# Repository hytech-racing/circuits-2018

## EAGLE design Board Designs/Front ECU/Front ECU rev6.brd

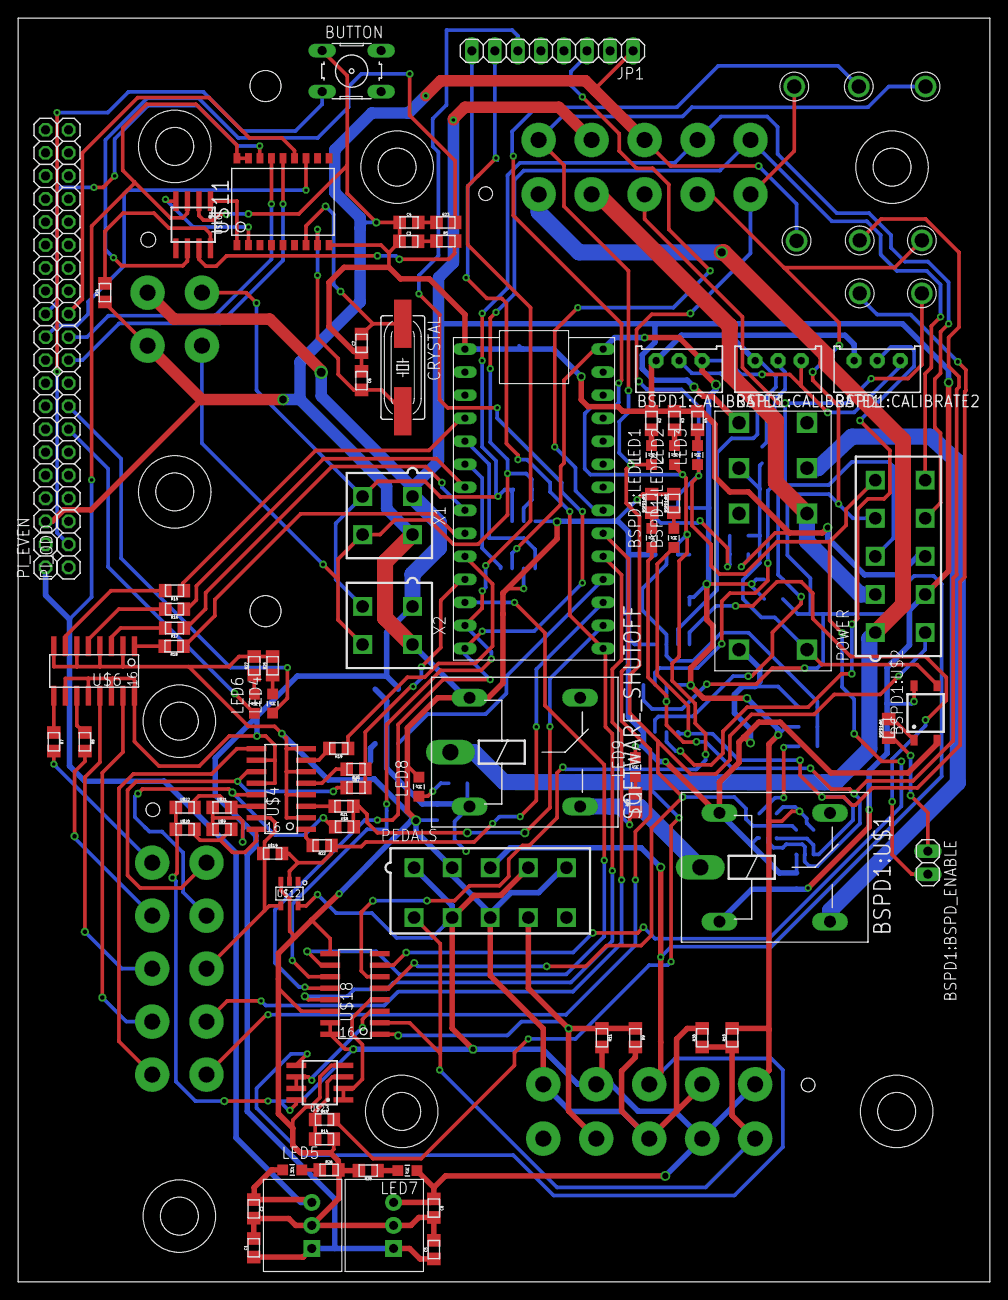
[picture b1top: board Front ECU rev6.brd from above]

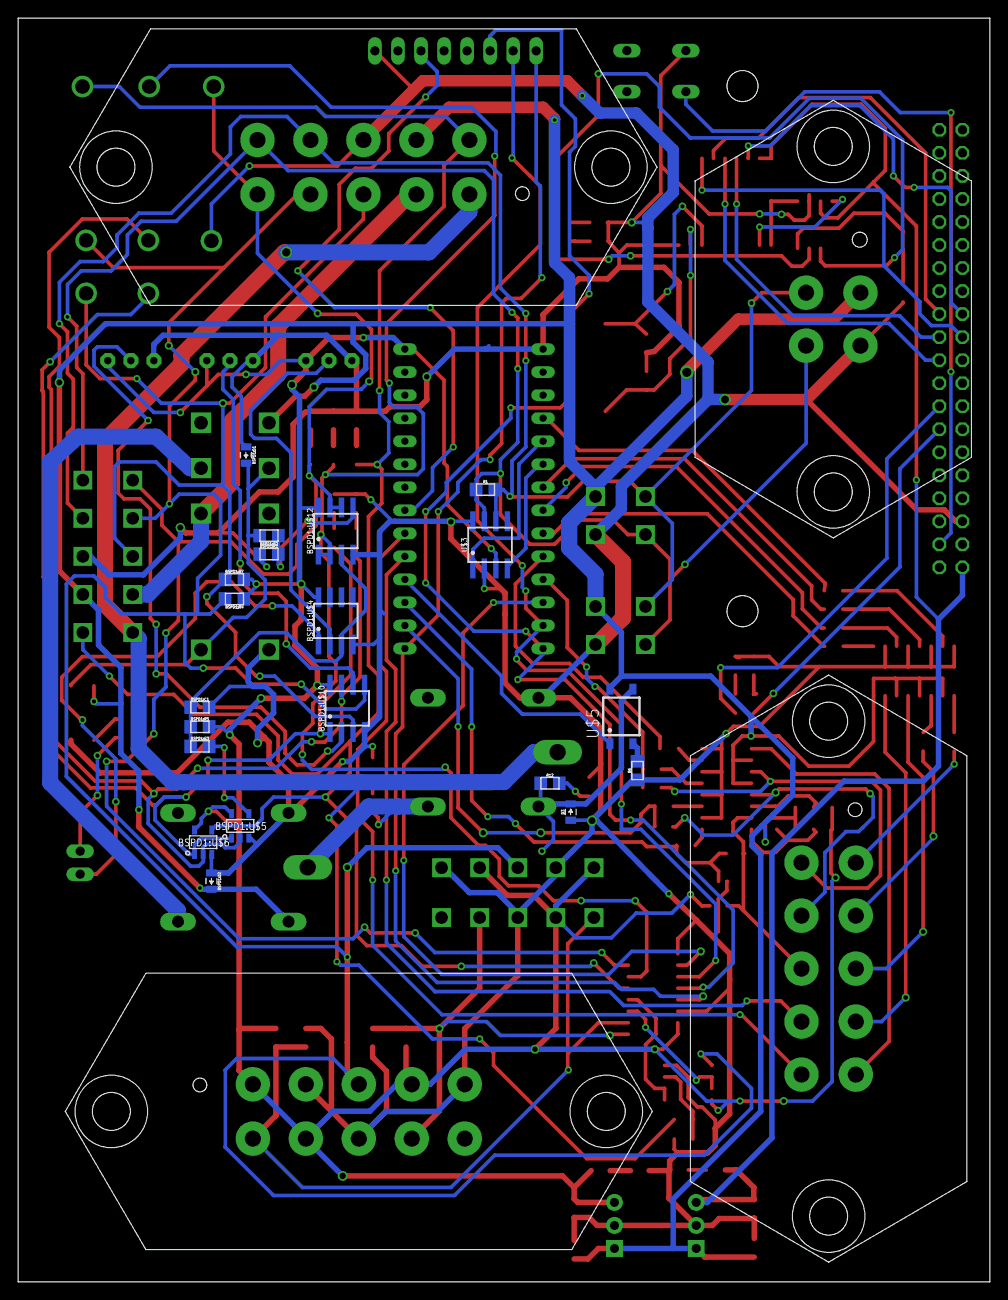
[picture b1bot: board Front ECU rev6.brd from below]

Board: 2 copper layers, 107.2 x 139.4 mm, 115 parts (24 on the bottom side), 100 nets.

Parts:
BSPD1:BSPD_ENABLE: JUMPER; 1X02
BSPD1:C1: .47u; 0805
BSPD1:CALIBRATE1, BSPD1:CALIBRATE2, BSPD1:CALIBRATE3: TRIMPOT_3296
BSPD1:D1, BSPD1:D2: DIODE0805; 0805_D
BSPD1:LED1: RED; LED-805
BSPD1:LED2: YELLOW; LED-805
BSPD1:R1: 12k; 0805
BSPD1:R2: 43k; 0805
BSPD1:R3: 330; 0805
BSPD1:R4, BSPD1:R7: 10k; 0805
BSPD1:R5: 680k; 0805
BSPD1:R6: 680; 0805
BSPD1:R8, BSPD1:R9: 270; 0805
BSPD1:U$1: G5LE; ZF112
BSPD1:U$2: CPC1002N; SOP04
BSPD1:U$3: JW2SN-DC12V; JW2SN
BSPD1:U$4, BSPD1:U$10: MCP6542SOIC; SOIC-08
BSPD1:U$5: SN74AHC1G09; SOT-23-5
BSPD1:U$6: SN74LVC1G08; SOT-23-5
BSPD1:U$11, BSPD1:U$13: TEST_POINT
BSPD1:U$12: MCP6002SOIC; SOIC-08
BUTTON: B3F-10XX
C1, C2, C5, C8: 10uF; 0805
C3, C4: 560pF; 0805
C6, C7: 22pF; 0805
CRYSTAL: 16MHz; HC49UP
D3: DIODE0805; 0805_D
IC2, IC3: OKI-78SR
JP1: 1X08
LED1, LED6, LED8, LED9: RED; LED-805
LED2: YELLOW; LED-805
LED3, LED4: GREEN; LED-805
LED5, LED7: PURPLE; LED-805
PEDALS: MINIFIT_5566-10
PI_EVEN: 1X20
PI_ODD: 1X20
POWER: MINIFIT_5566-10
R1: 120; 0805
R2, R3, R15, R16, R17, R18, R19, R20, R21, R22, R27: 270; 0805
R4, R25, R26, R28: 200; 0805
R5, R23: 100; 0805
R6: 330; 0805
R7, R8: 0; 0805
R9, R10, R11, R30: 10k; 0805
R12, R29: 1.2K; 0805
R13: 43k; 0805
R14: 12k; 0805
R24: 4.7k; 0805
SOFTWARE_SHUTOFF: G5LE; ZF112
U$1: TEENSY_3.2_SIMPLE
U$2, U$13, U$14, U$15, U$16, U$17: TEST_POINT
U$3, U$10: MCP2551; SOIC-08
U$4, U$6: TLP291-4; SOIC-16
U$5: CPC1002N; SOP04
U$7, U$8, U$9, U$19, U$20, U$21, U$22: JUMPER; 0805
U$11: MCP2515SMD; SOIC-18W
U$12: SN74LV1T34; SOT-23-5
U$18: MCP3208SOIC; SOIC-16
U$23: MCP6002SOIC; SOIC-08
X1, X2: CONNECTOR-4; MINIFIT_5566-4
X3: CONNECTOR-4MX150L_VERTICAL-4; MX150L_VERTICAL-4
X4, X5, X6: CONNECTOR-10MX150L_VERTICAL-10; MX150L_VERTICAL-10

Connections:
+5V: BSPD1:CALIBRATE1.1, BSPD1:CALIBRATE2.1, BSPD1:CALIBRATE3.1, BSPD1:R4.1, BSPD1:R5.2, BSPD1:R7.2, BSPD1:U$4.8, BSPD1:U$5.5, BSPD1:U$6.5, BSPD1:U$10.8, BSPD1:U$12.8, C8.1, IC3.3, LED7.A, PEDALS.1, PEDALS.4, PEDALS.7, R10.2, R11.2, U$1.VIN, U$3.3, U$12.5, U$18.15, U$18.16, U$20.1, U$22.1, U$23.8, X4.1, X4.4, X4.7
+5V/1: C2.1, IC2.3, LED5.A, PI_EVEN.1, U$10.3, U$11.17, U$11.18
+12V: BSPD1:D2.C, BSPD1:U$1.2, BSPD1:U$2.4, BSPD1:U$3.4, C1.1, C5.1, IC2.1, IC3.1, POWER.7, U$4.10, U$4.12, U$5.4, U$6.10, U$6.12, U$6.14, U$6.16, U$9.1, U$21.1, X1.1, X2.1, X3.1, X5.7
BSPD1:N$1: BSPD1:D1.C, BSPD1:R2.2, BSPD1:U$2.3, BSPD1:U$3.3, BSPD1:U$3.COIL-
BSPD1:N$2: BSPD1:R3.2, BSPD1:U$5.4
BSPD1:N$3: BSPD1:R6.2, BSPD1:U$2.1
BSPD1:N$4: BSPD1:BSPD_ENABLE.1, BSPD1:R6.1
BSPD1:N$5: BSPD1:CALIBRATE2.2, BSPD1:U$10.2
BSPD1:N$6: BSPD1:CALIBRATE1.2, BSPD1:U$10.6
BSPD1:N$7: BSPD1:CALIBRATE3.2, BSPD1:U$4.2
BSPD1:N$8: BSPD1:BSPD_ENABLE.2, BSPD1:U$4.1
BSPD1:N$9: BSPD1:R1.2, BSPD1:R2.1, BSPD1:U$12.5
BSPD1:N$13: BSPD1:C1.1, BSPD1:R3.1, BSPD1:R5.1, BSPD1:U$4.3, BSPD1:U$12.3
BSPD1:N$14: BSPD1:LED2.C, BSPD1:R8.1
BSPD1:N$15: BSPD1:LED1.C, BSPD1:R9.1
BSPD1:N$16: BSPD1:LED1.A, BSPD1:U$5.2, BSPD1:U$6.2, BSPD1:U$10.7, BSPD1:U$11.P$1
BSPD1:N$17: BSPD1:LED2.A, BSPD1:U$5.1, BSPD1:U$6.1, BSPD1:U$10.1, BSPD1:U$13.P$1
BSPD1:SHUTDOWN_C: BSPD1:U$1.S, BSPD1:U$3.6
BUT: BUTTON.3, PI_ODD.2
CAN-H: R5.2, U$10.7
CAN-L: R23.2, U$10.6
CANH: POWER.10, R1.1, U$3.7, X1.4, X2.4, X3.4, X5.10
CANL: POWER.9, R1.2, U$3.6, X1.3, X2.3, X3.3, X5.9
CS: PI_EVEN.12, U$11.16
CS_ADXL345: JP1.3, U$1.A5
CS_MCP3208: U$1.D10(TX2), U$18.10
DASH_CTRL1: R15.1, U$1.D2
DASH_CTRL2: R16.1, U$1.D5
DASH_CTRL3: R17.1, U$1.D6
DASH_CTRL4: R18.1, U$1.D7(RX3)
DASH_CTRL5: R19.1, U$1.D8(TX3)
DASH_CTRL6: R20.1, U$1.D9(RX2), U$7.2
DASH_CTRL7: R21.1, U$1.A0, U$8.2
DASH_CTRL8: R22.1, U$1.A1, U$12.2, U$19.2
DASH_CTRL9: U$1.A3, X6.9
DASH_CTRL10: U$1.A4, X6.10
DASH_IO1: R7.2, X6.1
DASH_IO2: R8.2, X6.2
DASH_IO3: U$6.13, X6.3
DASH_IO4: U$6.15, X6.4
DASH_IO5: U$4.9, X6.5
DASH_IO6: U$4.11, U$7.1, X6.6
DASH_IO7: U$4.13, U$8.1, X6.7
DASH_IO8: U$4.15, U$12.4, U$19.1, X6.8
GND: BSPD1:C1.2, BSPD1:CALIBRATE1.3, BSPD1:CALIBRATE2.3, BSPD1:CALIBRATE3.3, BSPD1:D1.A, BSPD1:D2.A, BSPD1:R1.1, BSPD1:R8.2, BSPD1:R9.2, BSPD1:U$1.1, BSPD1:U$2.2, BSPD1:U$3.COIL+, BSPD1:U$4.4, BSPD1:U$5.3, BSPD1:U$6.3, BSPD1:U$10.4, BSPD1:U$12.4, BUTTON.1, C1.2, C2.2, C3.1, C4.1, C5.2, C6.1, C7.1, C8.2, D3.A, IC2.2, IC3.2, JP1.1, LED8.C, LED9.C, PEDALS.2, PEDALS.5, PEDALS.8, PI_EVEN.3, POWER.8, R2.1, R3.1, R4.1, R6.1, R9.2, R14.2, R24.1, R25.2, R26.2, R27.2, R28.2, R30.2, SOFTWARE_SHUTOFF.1, U$1.GND, U$2.P$1, U$3.2, U$3.8, U$4.2, U$4.4, U$4.6, U$4.8, U$6.2, U$6.4, U$6.6, U$6.8, U$10.2, U$11.9, U$12.3, U$18.9, U$18.14, U$23.4, X1.2, X2.2, X3.2, X4.2, X4.5, X4.8, X5.8
INT: PI_EVEN.11, U$11.12
LED1: LED4.A, PI_ODD.8
LED2: LED6.A, PI_ODD.7
MISO: PI_ODD.11, U$11.15
MISO_TEENSY: JP1.6, U$1.D12, U$18.12
MOSI: PI_ODD.10, U$11.14
MOSI_TEENSY: JP1.7, U$1.D11, U$18.11
unnamed: R7.1, U$6.9
unnamed: U$1.D4(CANRX), U$3.4
unnamed: R8.1, U$6.11
unnamed: U$4.16, U$9.2, U$20.2
unnamed: U$1.D3(CANTX), U$3.1
unnamed: U$4.14, U$21.2, U$22.2
unnamed: R13.1, R14.1, U$23.3
unnamed: LED8.A, R12.2
unnamed: LED9.A, R29.2
unnamed: D3.C, R12.1, SOFTWARE_SHUTOFF.2, U$5.3
unnamed: LED1.C, R2.2
unnamed: LED2.C, R3.2
unnamed: LED3.C, R4.2
unnamed: R15.2, U$6.7
unnamed: R6.2, U$5.2
unnamed: R16.2, U$6.5
unnamed: R21.2, U$4.3
unnamed: R17.2, U$6.3
unnamed: R18.2, U$6.1
unnamed: R19.2, U$4.7
unnamed: R20.2, U$4.5
unnamed: R22.2, U$4.1
unnamed: U$10.1, U$11.1
unnamed: U$10.4, U$11.2
unnamed: C6.2, CRYSTAL.2, U$11.8
unnamed: R24.2, U$10.8
unnamed: C7.2, CRYSTAL.1, U$11.7
unnamed: C3.2, R5.1
unnamed: C4.2, R23.1
unnamed: LED4.C, R25.1
unnamed: LED5.C, R26.1
unnamed: LED6.C, R27.1
unnamed: LED7.C, R28.1
READ_BRAKE: U$18.3, U$23.6, U$23.7
READ_CHARGE: BSPD1:U$12.1, BSPD1:U$12.2, LED2.A, U$16.P$1, U$18.6
READ_FAULT: BSPD1:U$12.6, BSPD1:U$12.7, LED3.A, POWER.5, U$15.P$1, U$18.7, X5.5
READ_SWITCH: BSPD1:U$6.4, LED1.A, POWER.6, U$17.P$1, U$18.5, X5.6
READ_UPSTREAM_SHUTDOWN: U$18.4, U$23.1, U$23.2
SCK: PI_ODD.12, U$11.13
SCK_TEENSY: JP1.8, U$1.D13, U$18.13
SHUTDOWN_A: POWER.1, R13.2, SOFTWARE_SHUTOFF.P, X5.1
SHUTDOWN_B: BSPD1:U$1.P, R29.1, SOFTWARE_SHUTOFF.S
SHUTDOWN_D: BSPD1:U$3.7, POWER.2, X5.2
SHUTDOWN_RELAY_CTRL: U$1.A2, U$5.1
SIGNAL_ACCEL1: PEDALS.9, R9.1, R11.1, U$18.1, X4.9
SIGNAL_ACCEL2: PEDALS.6, R10.1, R30.1, U$18.2, X4.6
SIGNAL_BRAKE: BSPD1:R4.2, BSPD1:U$10.5, PEDALS.3, POWER.4, U$13.P$1, U$23.5, X4.3, X5.4
SIGNAL_CURRENT: BSPD1:R7.1, BSPD1:U$10.3, POWER.3, U$14.P$1, X5.3

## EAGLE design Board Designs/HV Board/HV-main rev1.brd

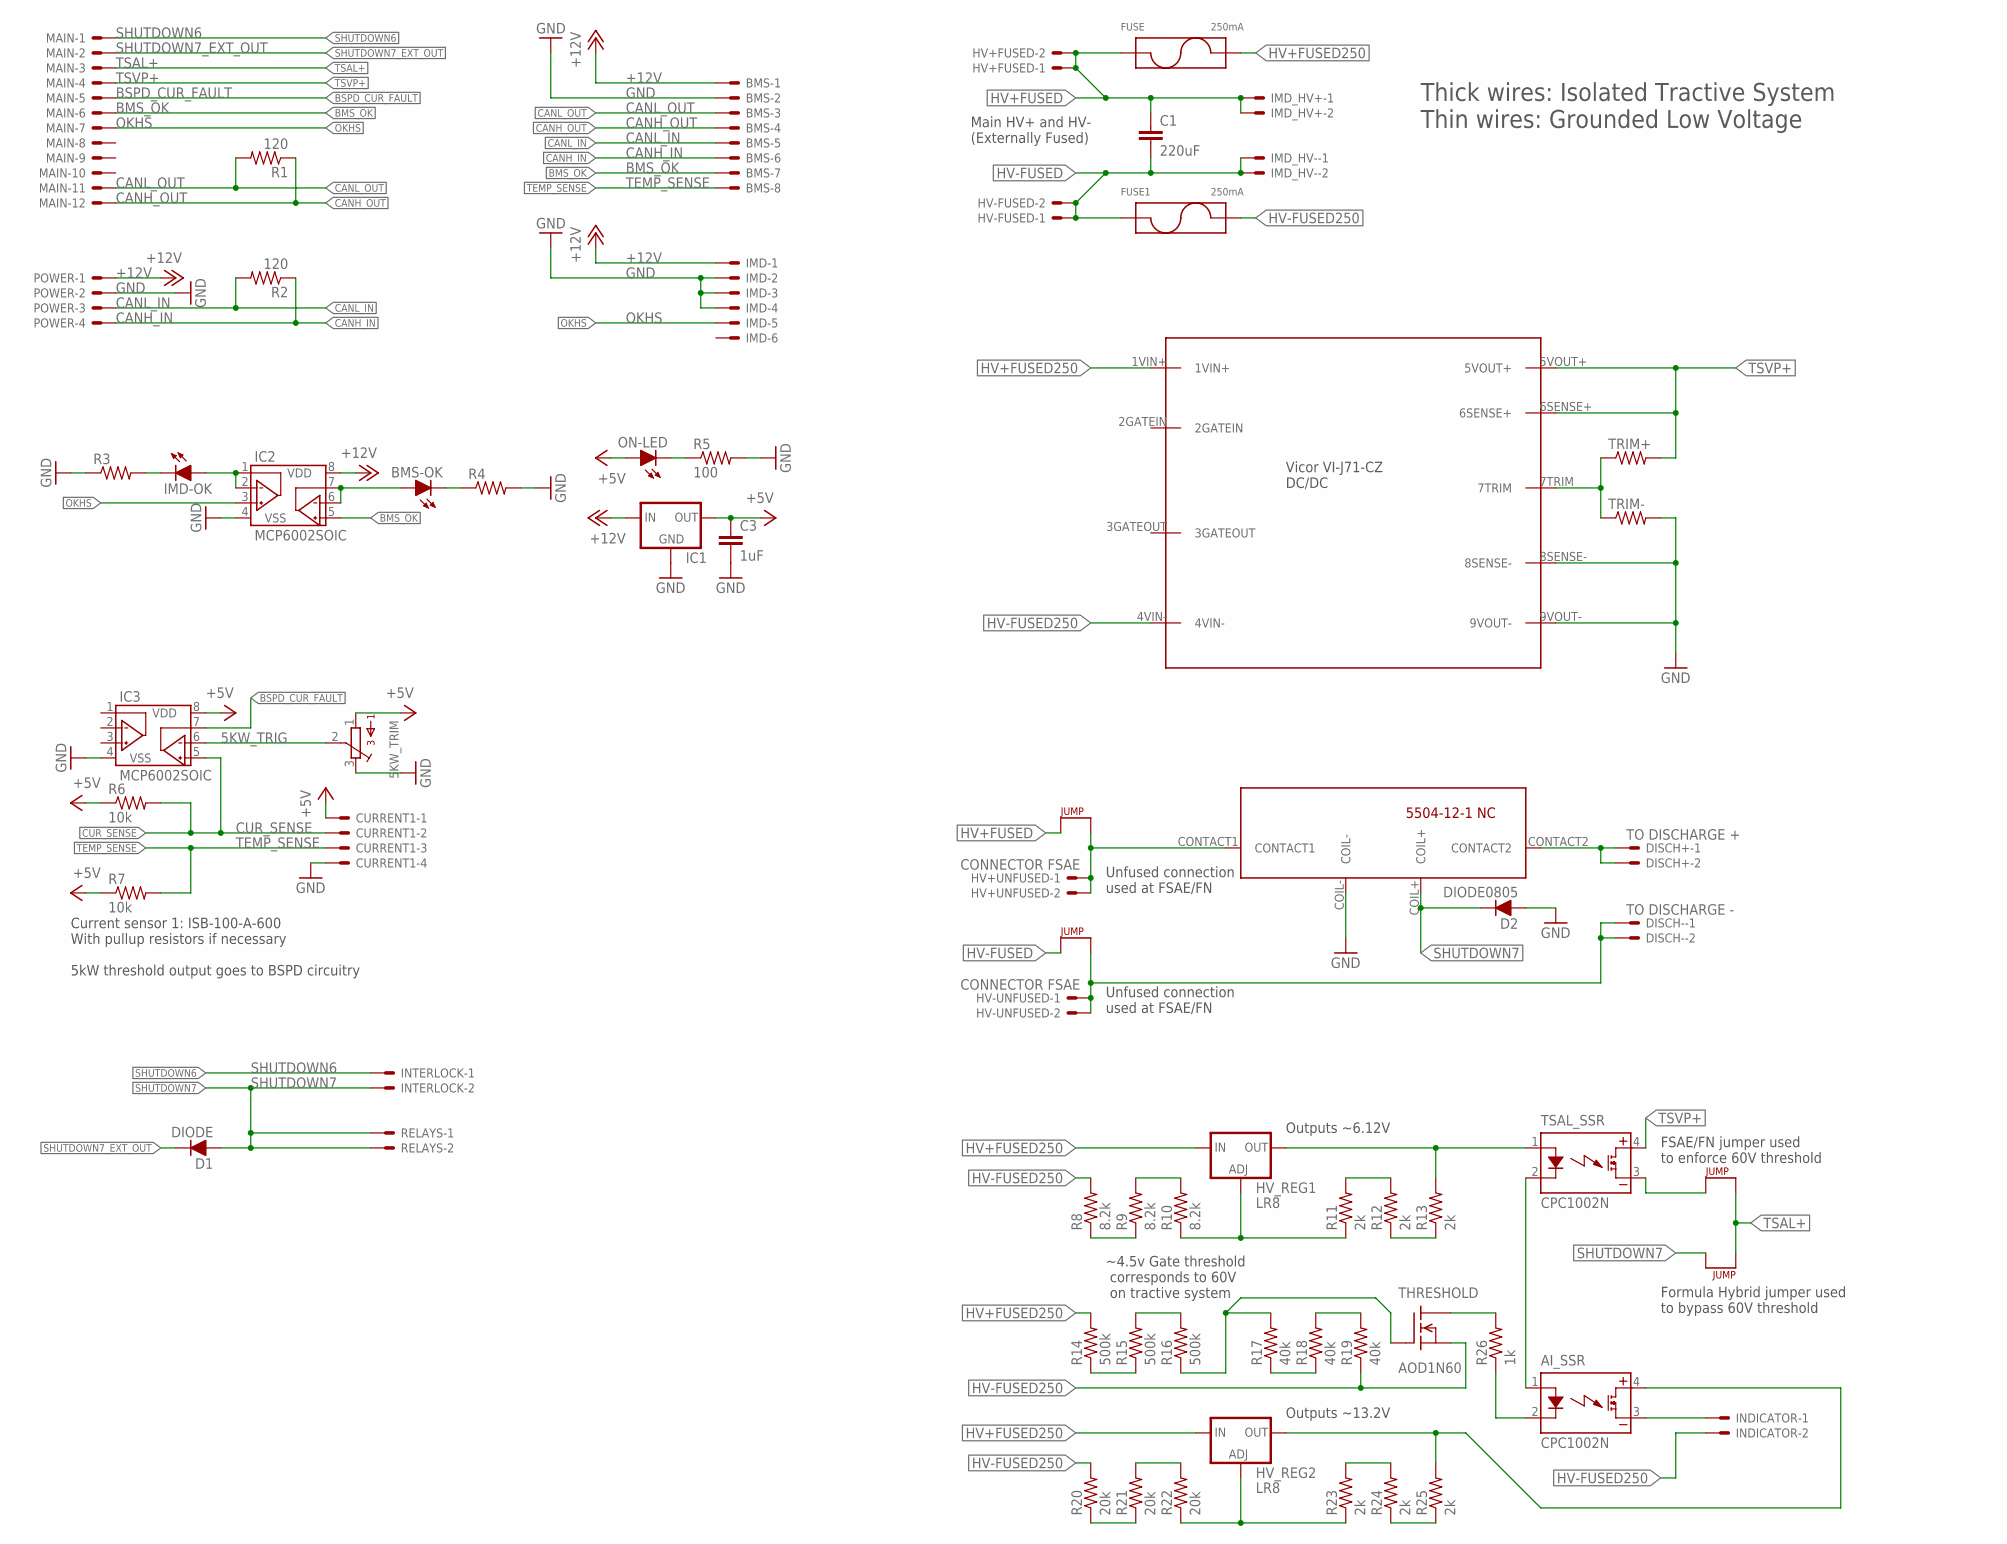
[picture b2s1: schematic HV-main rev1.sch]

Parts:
5KW_TRIM: TRIMPOT_3296C; TRIMPOT_3296
AI_SSR: CPC1002N; SOP04
BMS: MINIFIT_5566-8
BMS-OK: LED-0805; LED-805
C1: 220uF; LLS2V221MELZ
C3: 1uF; 0805
CURRENT1: MINIFIT_5566-4
D1: DIODE; DO-41
D2: DIODE0805; 0805_D
DISCH+: TO DISCHARGE +; MINIFIT_5566-2
DISCH-: TO DISCHARGE -; MINIFIT_5566-2
FUSE, FUSE1: 250mA; 1A3400_38.1MM
HV+FUSED: MINIFIT_5566-2
HV+UNFUSED: CONNECTOR FSAE; MINIFIT_5566-2
HV-FUSED: MINIFIT_5566-2
HV-UNFUSED: CONNECTOR FSAE; MINIFIT_5566-2
HV_REG1, HV_REG2: LR8; TO-252
IC1: 5VREG_L7805_VERT; TO-220
IC2, IC3: MCP6002SOIC; SOIC-08
IMD: CONNECTOR-6; MINIFIT_5566-6
IMD-OK: LED-0805; LED-805
IMD_HV+: CONNECTOR-2; MINIFIT_5566-2
IMD_HV-: CONNECTOR-2; MINIFIT_5566-2
INDICATOR: MINIFIT_5566-2
INTERLOCK: MINIFIT_5566-2
MAIN: CONNECTOR-12; MINIFIT_5566-12
ON-LED: LED-0805; LED-805
POWER: MINIFIT_5566-4
R1, R2: 120; 0805
R3, R4: RESISTOR0805-RES; 0805
R5: 100; 0805
R6, R7: 10k; 0805
R8, R9, R10: 8.2k; 0805
R11, R12, R13, R23, R24, R25: 2k; 0805
R14, R15, R16: 500k; 0805
R17, R18, R19: 40k; 0805
R20, R21, R22: 20k; 0805
R26: 1k; 0805
RELAYS: MINIFIT_5566-2
THRESHOLD: AOD1N60; TO-252
TRIM+: RESISTOR0805-RES; 0805
TRIM-: RESISTOR0805-RES; 0805
TSAL_SSR: CPC1002N; SOP04
U$1, U$2, U$3, U$4: JUMPER.3; AXIAL-0.3
U$5: HV_DCDC_VI-J71-CZ
U$12: 5504-12-1-NC

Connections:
5KW_TRIG: 5KW_TRIM.2, IC3.6 (VINB-)
+5V: 5KW_TRIM.1, C3.1, CURRENT1.1, IC1.3 (OUT), IC3.8 (VDD), ON-LED.A, R6.1, R7.1
+12V: BMS.1, IC1.1 (IN), IC2.8 (VDD), IMD.1, POWER.1
BMS_OK: BMS.7, IC2.5 (VINB+), MAIN.6
BSPD_CUR_FAULT: IC3.7 (VOUTB), MAIN.5
CANH_IN: BMS.6, POWER.4, R2.1
CANH_OUT: BMS.4, MAIN.12, R1.1
CANL_IN: BMS.5, POWER.3, R2.2
CANL_OUT: BMS.3, MAIN.11, R1.2
CUR_SENSE: CURRENT1.2, IC3.5 (VINB+), R6.2
DISCHARGE1: HV+UNFUSED.1, HV+UNFUSED.2, U$3.P$2, U$12.CONTACT1
DISCHARGE2: DISCH+.1, DISCH+.2, U$12.CONTACT2
DISCHARGE3: DISCH-.1, DISCH-.2, HV-UNFUSED.1, HV-UNFUSED.2, U$4.P$2
GND: 5KW_TRIM.3, BMS.2, C3.2, CURRENT1.4, D2.A, IC1.2 (GND), IC2.4 (VSS), IC3.4 (VSS), IMD.2, IMD.3, IMD.4, POWER.2, R3.1, R4.2, R5.2, TRIM-.2, U$5.8SENSE-, U$5.9VOUT-, U$12.COIL-
HV+FUSED: C1.P$1 (1), FUSE.P1, FUSE.P2 (P1), HV+FUSED.1, HV+FUSED.2, IMD_HV+.1, IMD_HV+.2, U$3.P$1
HV+FUSED250: FUSE.N3 (P2), FUSE.N4 (P2), HV_REG1.1 (IN), HV_REG2.1 (IN), R14.2, U$5.1VIN+
HV-FUSED: C1.P$2 (2), FUSE1.P1, FUSE1.P2 (P1), HV-FUSED.1, HV-FUSED.2, IMD_HV-.1, IMD_HV-.2, U$4.P$1
HV-FUSED250: FUSE1.N3 (P2), FUSE1.N4 (P2), INDICATOR.2, R8.2, R19.1, R20.2, THRESHOLD.3 (S), U$5.4VIN-
unnamed: AI_SSR.4 (DC+), HV_REG2.2(TAB) (OUT), R25.2
unnamed: HV_REG1.2(TAB) (OUT), R13.2, TSAL_SSR.1 (CONTROL+)
unnamed: ON-LED.C, R5.1
unnamed: TSAL_SSR.3 (DC-), U$1.P$1
unnamed: AI_SSR.2 (CONTROL-), R26.1
unnamed: AI_SSR.1 (CONTROL+), TSAL_SSR.2 (CONTROL-)
unnamed: AI_SSR.3 (DC-), INDICATOR.1
unnamed: R8.1, R9.1
unnamed: R26.2, THRESHOLD.2(TAB) (D)
unnamed: R14.1, R15.1
unnamed: R15.2, R16.2
unnamed: R17.1, R18.1
unnamed: R18.2, R19.2
unnamed: R9.2, R10.2
unnamed: HV_REG2.3 (ADJ), R22.1, R23.1
unnamed: R11.2, R12.2
unnamed: R12.1, R13.1
unnamed: HV_REG1.3 (ADJ), R10.1, R11.1
unnamed: R23.2, R24.2
unnamed: R24.1, R25.1
unnamed: R21.2, R22.2
unnamed: R16.1, R17.2, THRESHOLD.1 (G)
unnamed: R20.1, R21.1
unnamed: IC2.1 (VOUTA), IC2.2 (VINA-), IMD-OK.A
unnamed: BMS-OK.A, IC2.6 (VINB-), IC2.7 (VOUTB)
unnamed: BMS-OK.C, R4.1
unnamed: IMD-OK.C, R3.2
OKHS: IC2.3 (VINA+), IMD.5, MAIN.7
SHUTDOWN6: INTERLOCK.1, MAIN.1
SHUTDOWN7: D1.A, D2.C, INTERLOCK.2, RELAYS.1, RELAYS.2, U$2.P$2, U$12.COIL+
SHUTDOWN7_EXT_OUT: D1.C, MAIN.2
TEMP_SENSE: BMS.8, CURRENT1.3, R7.2
TRIM: TRIM+.1, TRIM-.1, U$5.7TRIM
TSAL+: MAIN.3, U$1.P$2, U$2.P$1
TSVP+: MAIN.4, TRIM+.2, TSAL_SSR.4 (DC+), U$5.5VOUT+, U$5.6SENSE+

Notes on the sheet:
Formula Hybrid jumper used to bypass 60V threshold
Current sensor 1: ISB-100-A-600 With pullup resistors if necessary 5kW threshold output goes to BSPD circuitry
Unfused connection used at FSAE/FN
FSAE/FN jumper used to enforce 60V threshold
Main HV+ and HV- (Externally Fused)
~4.5v Gate threshold corresponds to 60V on tractive system
Thick wires: Isolated Tractive System Thin wires: Grounded Low Voltage
Outputs ~6.12V
Outputs ~13.2V

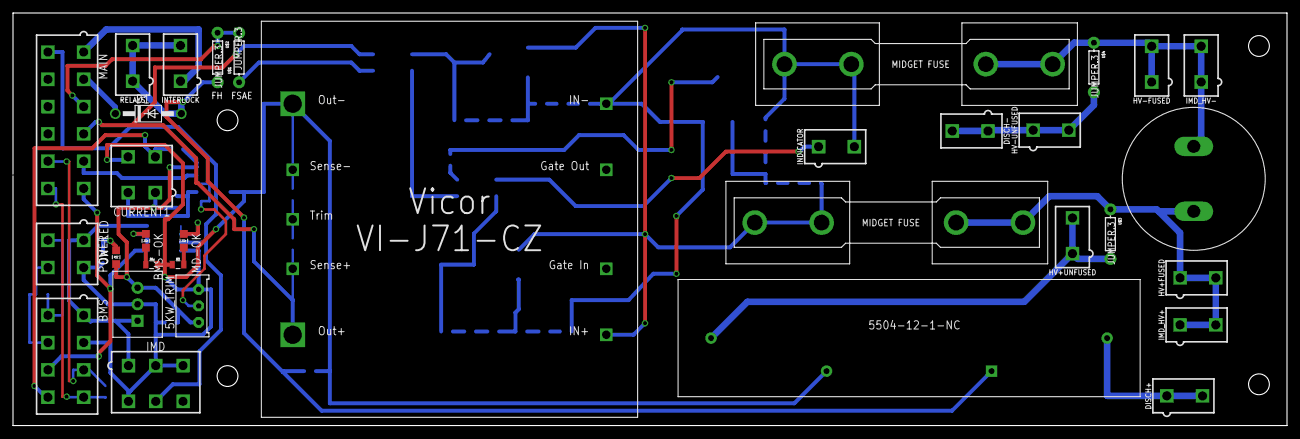
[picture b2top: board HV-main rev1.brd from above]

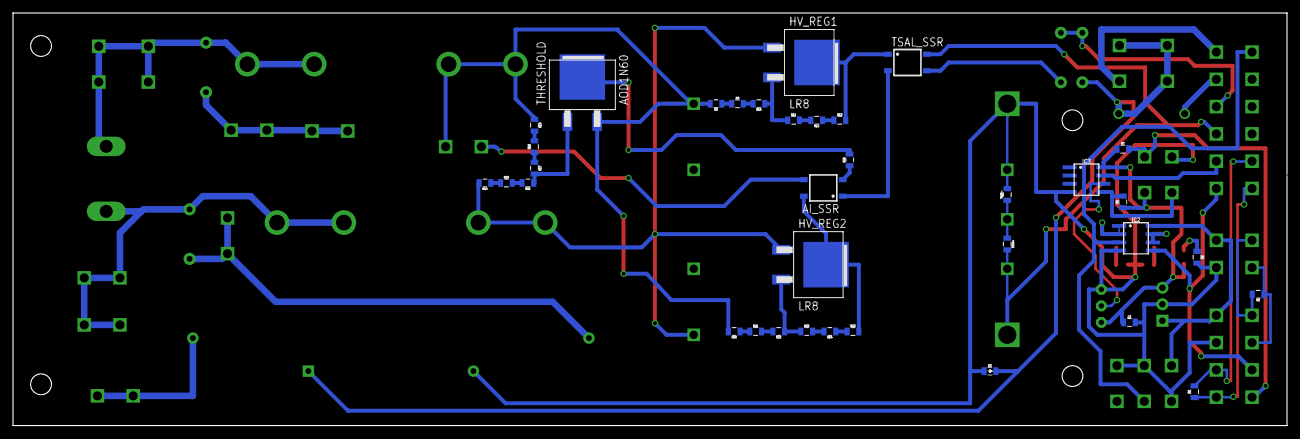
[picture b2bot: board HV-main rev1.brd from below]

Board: 2 copper layers, 196.1 x 63.5 mm, 68 parts (35 on the bottom side), 53 nets.

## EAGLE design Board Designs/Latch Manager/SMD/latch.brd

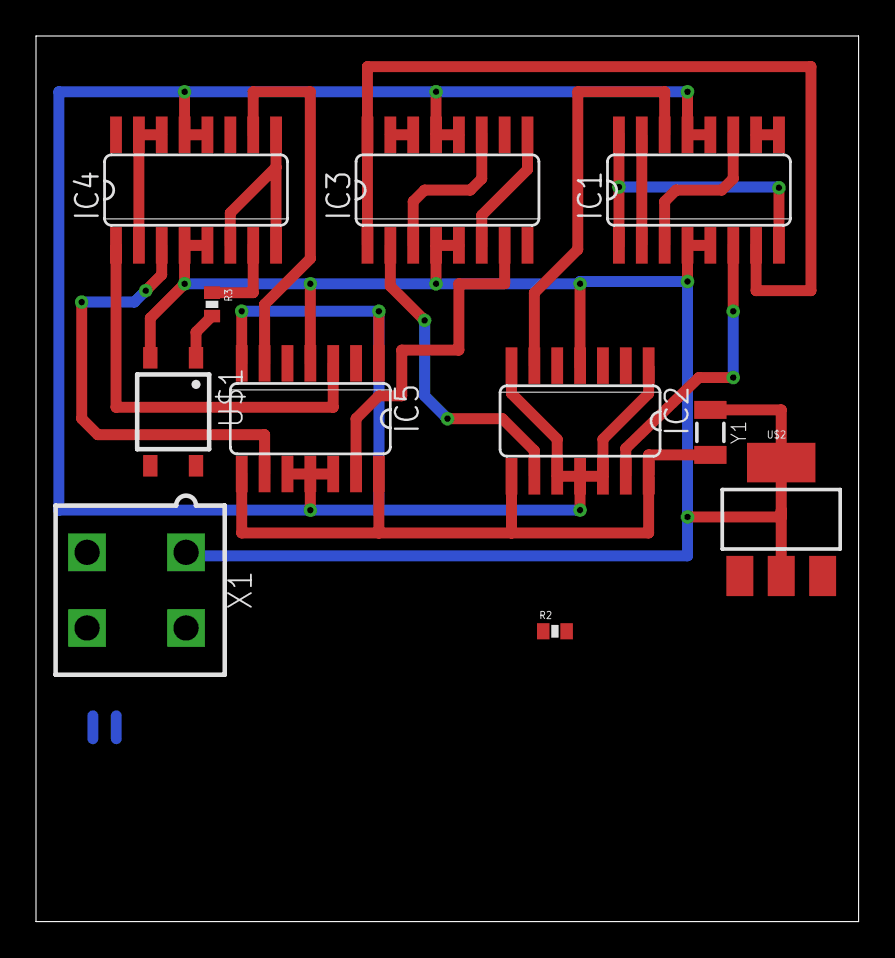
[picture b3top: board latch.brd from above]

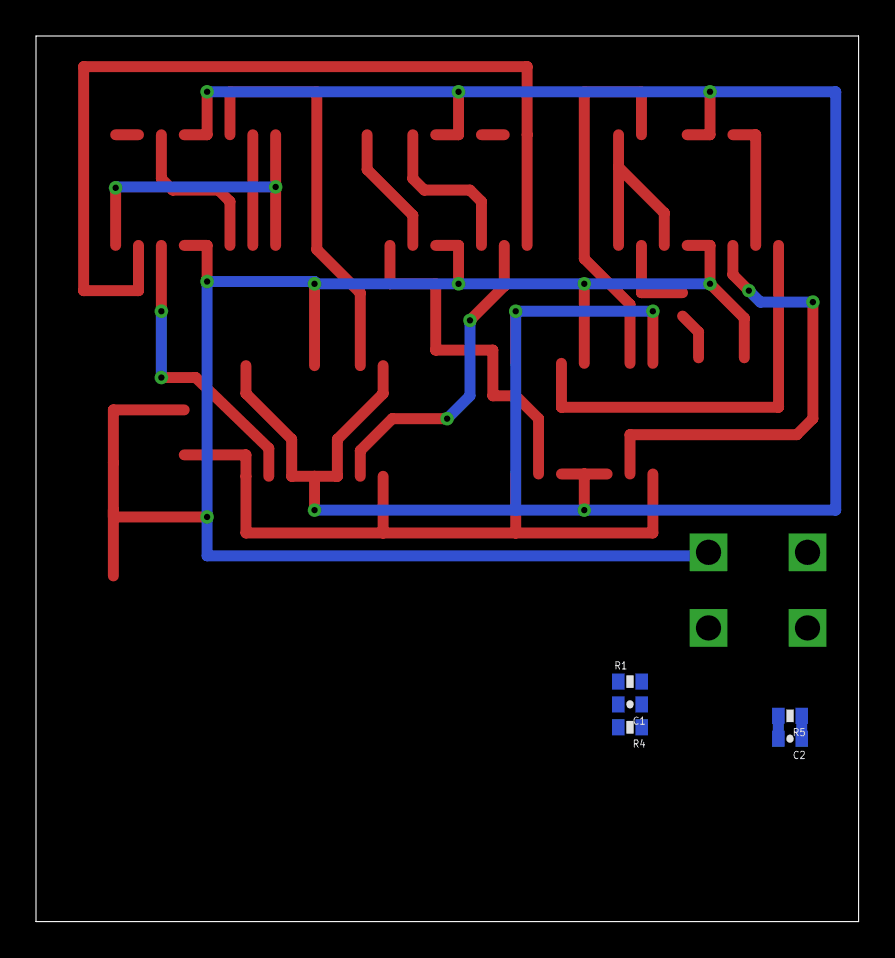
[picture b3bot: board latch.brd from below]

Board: 2 copper layers, 45.7 x 49.2 mm, 16 parts (5 on the bottom side), 25 nets.

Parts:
C1, C2: 0402-CAP
IC1, IC3, IC4: 74AC11000D; SO16
IC2, IC5: 74AC11074D; SO14
R1, R2, R3, R4, R5: 0402-RES
U$1: CPC1002N; SOP04
U$2: SOT223
X1: CONNECTOR-4; MINIFIT_5566-4
Y1: 16MHz; CRYSTAL-SMD-3.2X1.5MM

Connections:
+5V: IC1.12, IC1.13, IC2.1, IC2.7, IC2.10, IC2.11, IC2.12, IC3.12, IC3.13, IC4.12, IC4.13, IC5.1, IC5.7, IC5.10, IC5.11, IC5.12, R1.1, R2.2, U$2.3
GND: IC1.4, IC1.5, IC2.4, IC3.4, IC3.5, IC4.4, IC4.5, IC5.4, U$1.2, U$2.2, U$2.4, X1.1, Y1.P$1
unnamed: C2.1, R2.1, R5.1, X1.4
unnamed: IC1.2, IC1.15
unnamed: C2.2, IC1.1, IC1.8, IC1.16, R5.2
unnamed: IC1.3, IC1.11
unnamed: IC1.9, IC1.10, IC2.3
unnamed: IC1.6, IC2.13
unnamed: IC2.8, IC2.14, IC5.8, IC5.14, Y1.P$2
unnamed: IC2.9, IC3.2
unnamed: IC1.14, IC2.6, IC4.11
unnamed: IC4.3, IC5.9
unnamed: IC1.7, IC3.1, IC3.16
unnamed: IC4.7, R3.1
unnamed: R3.2, U$1.1
unnamed: C1.2, IC3.14, IC3.15, R4.2
unnamed: C1.1, R1.2, R4.1, X1.3
unnamed: U$2.1, X1.2
unnamed: IC3.3, IC3.11
unnamed: IC3.6, IC3.9
unnamed: IC3.8, IC4.1, IC5.3
unnamed: IC3.7, IC5.13
unnamed: IC3.10, IC4.10, IC5.6
unnamed: IC4.2, IC4.14, IC4.15
unnamed: IC4.6, IC4.8, IC4.9

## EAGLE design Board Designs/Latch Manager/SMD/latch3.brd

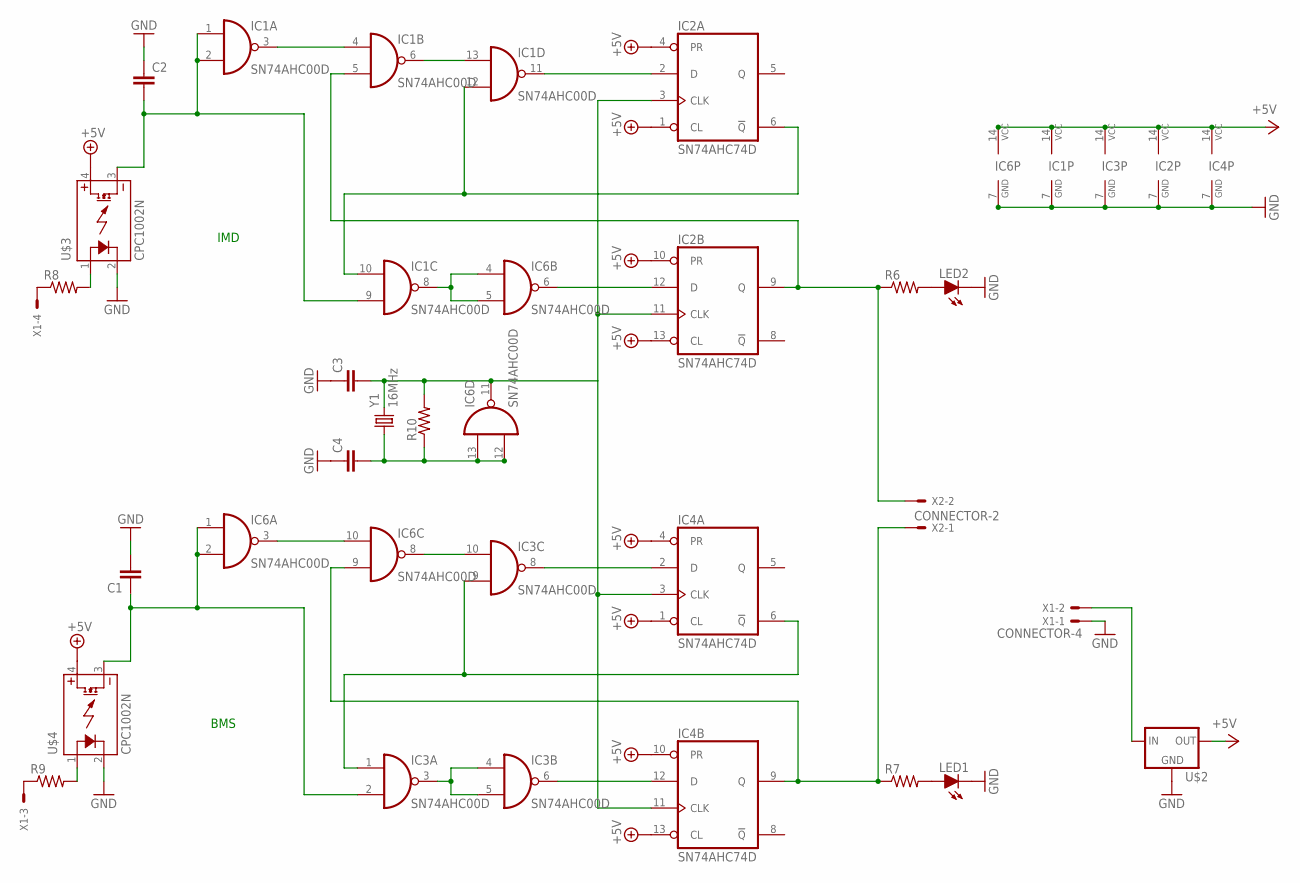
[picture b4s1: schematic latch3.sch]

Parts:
C1, C2, C3, C4: CAP0402-CAP; 0402-CAP
IC1, IC3, IC6: SN74AHC00D; SOIC-14
IC2, IC4: SN74AHC74D; SOIC-14
LED1, LED2: LED-0805; LED-805
R6, R7, R8, R9, R10: RESISTOR0402; 0402-RES
U$2: 5VREG_LM340-NLM340MPX-5.0/NOPB; SOT223
U$3, U$4: CPC1002N; SOP04
X1: CONNECTOR-4; MINIFIT_5566-4
X2: CONNECTOR-2; MINIFIT_5566-2
Y1: 16MHz; CRYSTAL-SMD-3.2X1.5MM

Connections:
12V: U$2.1 (IN), X1.2
+5V: IC1.14 (VCC), IC2.1 (CL), IC2.4 (PR), IC2.10 (PR), IC2.13 (CL), IC2.14 (VCC), IC3.14 (VCC), IC4.1 (CL), IC4.4 (PR), IC4.10 (PR), IC4.13 (CL), IC4.14 (VCC), IC6.14 (VCC), U$2.3 (OUT), U$3.4 (DC+), U$4.4 (DC+)
BMS_5V: C1.1, IC3.2 (I1), IC6.1 (I0), IC6.2 (I1), U$4.3 (DC-)
BMS_IN: R9.2, U$4.1 (CONTROL+)
BMS_OUT: IC4.9 (Q), IC6.9 (I1), R7.1, X2.1
GND: C1.2, C2.1, C3.1, C4.1, IC1.7 (GND), IC2.7 (GND), IC3.7 (GND), IC4.7 (GND), IC6.7 (GND), LED1.C, LED2.C, U$2.2 (GND), U$2.4 (GND), U$3.2 (CONTROL-), U$4.2 (CONTROL-), X1.1
IMD_5V: C2.2, IC1.1 (I0), IC1.2 (I1), IC1.9 (I1), U$3.3 (DC-)
IMD_IN: R8.2, U$3.1 (CONTROL+)
IMD_OUT: IC1.5 (I1), IC2.9 (Q), R6.1, X2.2
unnamed: IC1.3 (O), IC1.4 (I0)
unnamed: IC1.6 (O), IC1.13 (I0)
unnamed: IC1.10 (I0), IC1.12 (I1), IC2.6 (!Q)
unnamed: IC1.11 (O), IC2.2 (D)
unnamed: C3.2, IC2.3 (CLK), IC2.11 (CLK), IC4.3 (CLK), IC4.11 (CLK), IC6.11 (O), R10.2, Y1.P$2 (2)
unnamed: IC2.12 (D), IC6.6 (O)
unnamed: IC3.6 (O), IC4.12 (D)
unnamed: IC1.8 (O), IC6.4 (I0), IC6.5 (I1)
unnamed: C4.2, IC6.12 (I1), IC6.13 (I0), R10.1, Y1.P$1 (1)
unnamed: IC6.3 (O), IC6.10 (I0)
unnamed: IC3.10 (I0), IC6.8 (O)
unnamed: IC3.1 (I0), IC3.9 (I1), IC4.6 (!Q)
unnamed: IC3.8 (O), IC4.2 (D)
unnamed: IC3.3 (O), IC3.4 (I0), IC3.5 (I1)
unnamed: LED1.A, R7.2
unnamed: LED2.A, R6.2
unnamed: R8.1, X1.4
unnamed: R9.1, X1.3

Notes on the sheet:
IMD
BMS

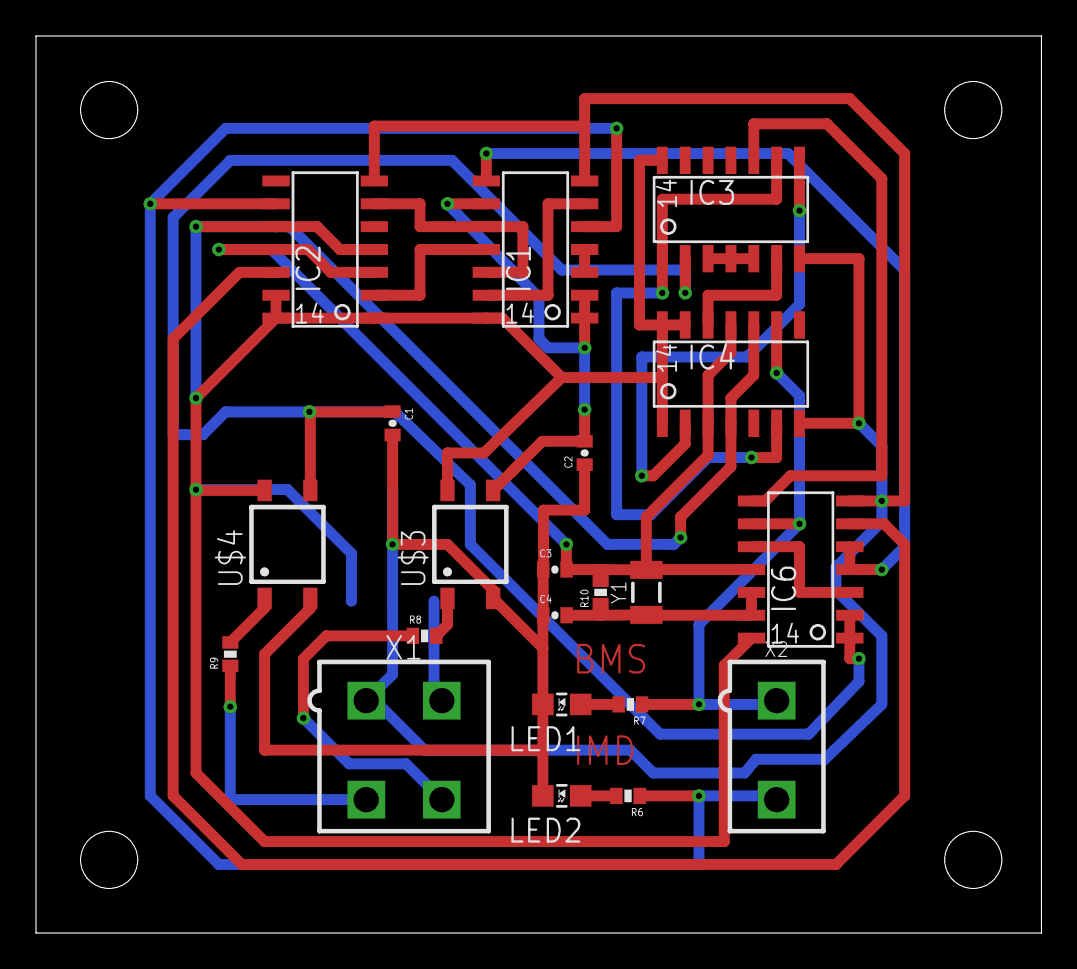
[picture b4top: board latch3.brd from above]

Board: 2 copper layers, 55.9 x 49.8 mm, 22 parts (1 on the bottom side), 27 nets.

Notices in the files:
parts and their libraries:
SparkFun-FreqCtrl: Licensing: Creative Commons ShareAlike 4.0 International - https://creativecommons.org/licenses/by-sa/4.0
